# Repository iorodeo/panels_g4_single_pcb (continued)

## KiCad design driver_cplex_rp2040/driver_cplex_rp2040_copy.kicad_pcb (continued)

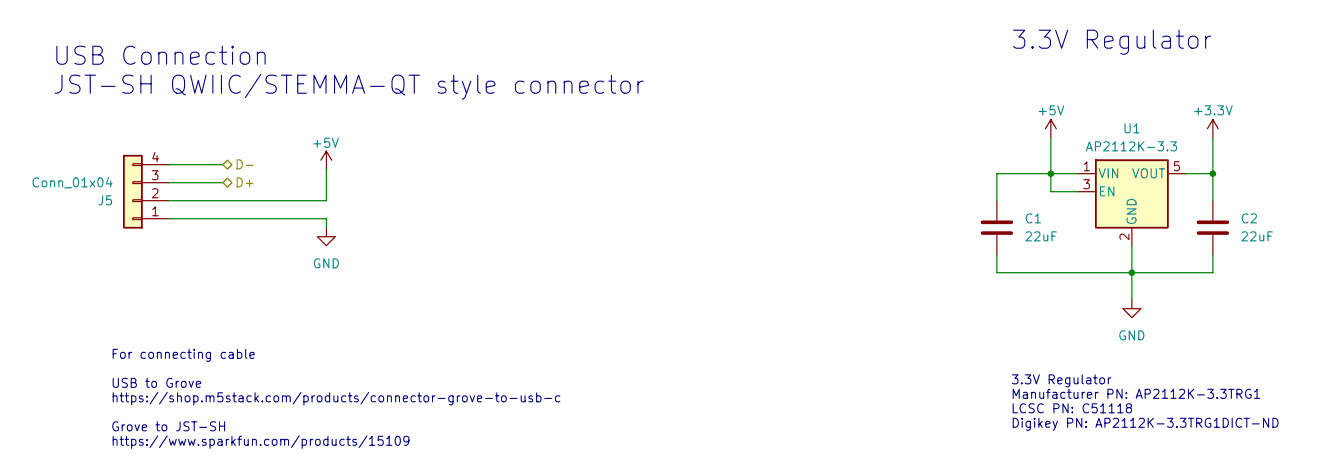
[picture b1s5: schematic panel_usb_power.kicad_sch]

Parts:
C1, C2: 22uF; C_0402_1005Metric
J5: Conn_01x04; JST_SH_SM04B-SRSS-TB_1x04-1MP_P1.00mm_Horizontal
U1: AP2112K-3.3; SOT-23-5

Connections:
+3.3V: C2.1, U1.5 (VOUT); also elsewhere on the board
+5V: C1.1, J5.2, U1.1 (VIN), U1.3 (EN); also elsewhere on the board
/panel_mcu/D+: J5.3; also elsewhere on the board
/panel_mcu/D-: J5.4; also elsewhere on the board
GND: C1.2, C2.2, J5.1, U1.2 (GND); also elsewhere on the board

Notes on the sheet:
USB Connection JST-SH QWIIC/STEMMA-QT style connector
For connecting cable USB to Grove https://shop.m5stack.com/products/connector-grove-to-usb-c Grove to JST-SH https://www.sparkfun.com/products/15109
3.3V Regulator
3.3V Regulator Manufacturer PN: AP2112K-3.3TRG1 LCSC PN: C51118 Digikey PN: AP2112K-3.3TRG1DICT-ND

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
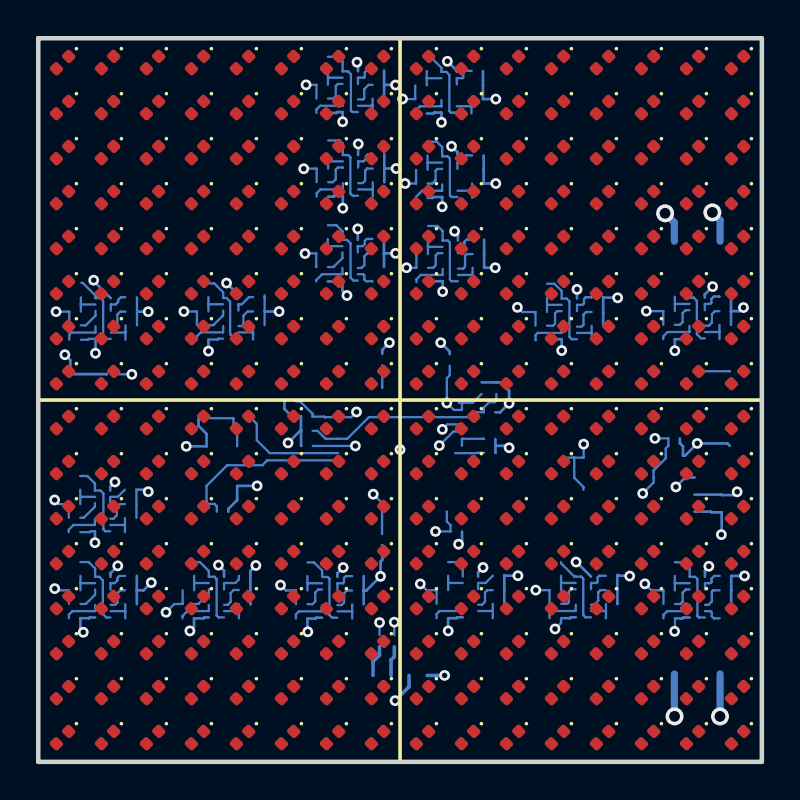
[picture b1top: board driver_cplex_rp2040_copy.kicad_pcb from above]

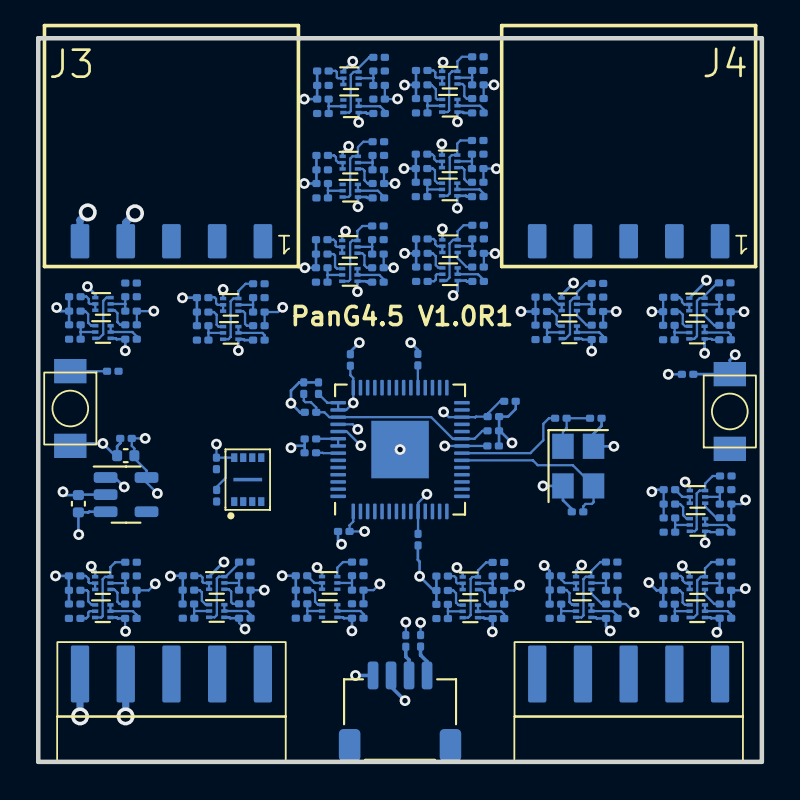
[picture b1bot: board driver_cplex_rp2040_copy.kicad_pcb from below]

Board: 6 copper layers, 40.2 x 40.2 mm, 479 parts (223 on the bottom side), 178 nets.

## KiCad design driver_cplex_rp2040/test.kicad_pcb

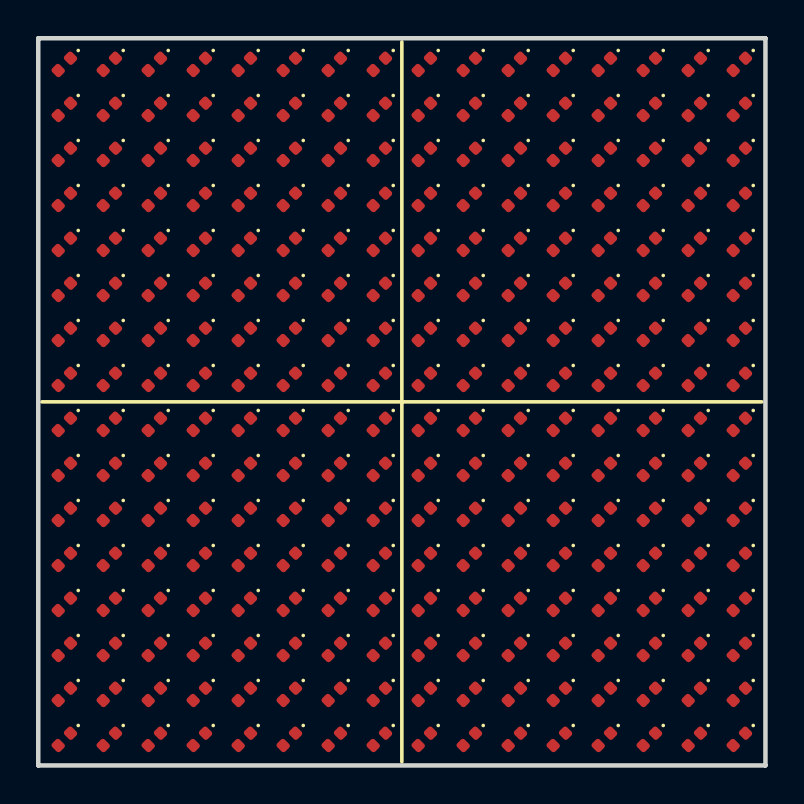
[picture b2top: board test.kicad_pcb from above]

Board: 6 copper layers, 40.4 x 40.4 mm, 256 parts (0 on the bottom side), 32 nets, no tracks yet.

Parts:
D1, D2, D3, D4, D5, D6, D7, D8, D9, D10, D11, D12, D13, D14, D15, D16, D17, D18, D19, D20, D21, D22, D23, D24, D25, D26, D27, D28, D29, D30, D31, D32, D33, D34, D35, D36, D37, D38, D39, D40, D41, D42, D43, D44, D45, D46, D47, D48, D49, D50, D51, D52, D53, D54, D55, D56, D57, D58, D59, D60, D61, D62, D63, D64, D65, D66, D67, D68, D69, D70, D71, D72, D73, D74, D75, D76, D77, D78, D79, D80, D81, D82, D83, D84, D85, D86, D87, D88, D89, D90, D91, D92, D93, D94, D95, D96, D97, D98, D99, D100, D101, D102, D103, D104, D105, D106, D107, D108, D109, D110, D111, D112, D113, D114, D115, D116, D117, D118, D119, D120, D121, D122, D123, D124, D125, D126, D127, D128, D129, D130, D131, D132, D133, D134, D135, D136, D137, D138, D139, D140, D141, D142, D143, D144, D145, D146, D147, D148, D149, D150, D151, D152, D153, D154, D155, D156, D157, D158, D159, D160, D161, D162, D163, D164, D165, D166, D167, D168, D169, D170, D171, D172, D173, D174, D175, D176, D177, D178, D179, D180, D181, D182, D183, D184, D185, D186, D187, D188, D189, D190, D191, D192, D193, D194, D195, D196, D197, D198, D199, D200, D201, D202, D203, D204, D205, D206, D207, D208, D209, D210, D211, D212, D213, D214, D215, D216, D217, D218, D219, D220, D221, D222, D223, D224, D225, D226, D227, D228, D229, D230, D231, D232, D233, D234, D235, D236, D237, D238, D239, D240, D241, D242, D243, D244, D245, D246, D247, D248, D249, D250, D251, D252, D253, D254, D255, D256: LED; LED_0402_1005Metric

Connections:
/panel_leds/ROW_00: D1.1 (K), D17.1 (K), D33.1 (K), D49.1 (K), D65.1 (K), D81.1 (K), D97.1 (K), D113.1 (K), D129.1 (K), D145.1 (K), D161.1 (K), D177.1 (K), D193.1 (K), D209.1 (K), D225.1 (K), D241.1 (K)
/panel_leds/ROW_01: D2.1 (K), D18.1 (K), D34.1 (K), D50.1 (K), D66.1 (K), D82.1 (K), D98.1 (K), D114.1 (K), D130.1 (K), D146.1 (K), D162.1 (K), D178.1 (K), D194.1 (K), D210.1 (K), D226.1 (K), D242.1 (K)
/panel_leds/ROW_02: D3.1 (K), D19.1 (K), D35.1 (K), D51.1 (K), D67.1 (K), D83.1 (K), D99.1 (K), D115.1 (K), D131.1 (K), D147.1 (K), D163.1 (K), D179.1 (K), D195.1 (K), D211.1 (K), D227.1 (K), D243.1 (K)
/panel_leds/ROW_03: D4.1 (K), D20.1 (K), D36.1 (K), D52.1 (K), D68.1 (K), D84.1 (K), D100.1 (K), D116.1 (K), D132.1 (K), D148.1 (K), D164.1 (K), D180.1 (K), D196.1 (K), D212.1 (K), D228.1 (K), D244.1 (K)
/panel_leds/ROW_04: D5.1 (K), D21.1 (K), D37.1 (K), D53.1 (K), D69.1 (K), D85.1 (K), D101.1 (K), D117.1 (K), D133.1 (K), D149.1 (K), D165.1 (K), D181.1 (K), D197.1 (K), D213.1 (K), D229.1 (K), D245.1 (K)
/panel_leds/ROW_05: D6.1 (K), D22.1 (K), D38.1 (K), D54.1 (K), D70.1 (K), D86.1 (K), D102.1 (K), D118.1 (K), D134.1 (K), D150.1 (K), D166.1 (K), D182.1 (K), D198.1 (K), D214.1 (K), D230.1 (K), D246.1 (K)
/panel_leds/ROW_06: D7.1 (K), D23.1 (K), D39.1 (K), D55.1 (K), D71.1 (K), D87.1 (K), D103.1 (K), D119.1 (K), D135.1 (K), D151.1 (K), D167.1 (K), D183.1 (K), D199.1 (K), D215.1 (K), D231.1 (K), D247.1 (K)
/panel_leds/ROW_07: D8.1 (K), D24.1 (K), D40.1 (K), D56.1 (K), D72.1 (K), D88.1 (K), D104.1 (K), D120.1 (K), D136.1 (K), D152.1 (K), D168.1 (K), D184.1 (K), D200.1 (K), D216.1 (K), D232.1 (K), D248.1 (K)
/panel_leds/ROW_08: D9.1 (K), D25.1 (K), D41.1 (K), D57.1 (K), D73.1 (K), D89.1 (K), D105.1 (K), D121.1 (K), D137.1 (K), D153.1 (K), D169.1 (K), D185.1 (K), D201.1 (K), D217.1 (K), D233.1 (K), D249.1 (K)
/panel_leds/ROW_09: D10.1 (K), D26.1 (K), D42.1 (K), D58.1 (K), D74.1 (K), D90.1 (K), D106.1 (K), D122.1 (K), D138.1 (K), D154.1 (K), D170.1 (K), D186.1 (K), D202.1 (K), D218.1 (K), D234.1 (K), D250.1 (K)
/panel_leds/ROW_10: D11.1 (K), D27.1 (K), D43.1 (K), D59.1 (K), D75.1 (K), D91.1 (K), D107.1 (K), D123.1 (K), D139.1 (K), D155.1 (K), D171.1 (K), D187.1 (K), D203.1 (K), D219.1 (K), D235.1 (K), D251.1 (K)
/panel_leds/ROW_11: D12.1 (K), D28.1 (K), D44.1 (K), D60.1 (K), D76.1 (K), D92.1 (K), D108.1 (K), D124.1 (K), D140.1 (K), D156.1 (K), D172.1 (K), D188.1 (K), D204.1 (K), D220.1 (K), D236.1 (K), D252.1 (K)
/panel_leds/ROW_12: D13.1 (K), D29.1 (K), D45.1 (K), D61.1 (K), D77.1 (K), D93.1 (K), D109.1 (K), D125.1 (K), D141.1 (K), D157.1 (K), D173.1 (K), D189.1 (K), D205.1 (K), D221.1 (K), D237.1 (K), D253.1 (K)
/panel_leds/ROW_13: D14.1 (K), D30.1 (K), D46.1 (K), D62.1 (K), D78.1 (K), D94.1 (K), D110.1 (K), D126.1 (K), D142.1 (K), D158.1 (K), D174.1 (K), D190.1 (K), D206.1 (K), D222.1 (K), D238.1 (K), D254.1 (K)
/panel_leds/ROW_14: D15.1 (K), D31.1 (K), D47.1 (K), D63.1 (K), D79.1 (K), D95.1 (K), D111.1 (K), D127.1 (K), D143.1 (K), D159.1 (K), D175.1 (K), D191.1 (K), D207.1 (K), D223.1 (K), D239.1 (K), D255.1 (K)
/panel_leds/ROW_15: D16.1 (K), D32.1 (K), D48.1 (K), D64.1 (K), D80.1 (K), D96.1 (K), D112.1 (K), D128.1 (K), D144.1 (K), D160.1 (K), D176.1 (K), D192.1 (K), D208.1 (K), D224.1 (K), D240.1 (K), D256.1 (K)
unnamed: D1.2 (A), D2.2 (A), D3.2 (A), D4.2 (A), D5.2 (A), D6.2 (A), D7.2 (A), D8.2 (A), D9.2 (A), D10.2 (A), D11.2 (A), D12.2 (A), D13.2 (A), D14.2 (A), D15.2 (A), D16.2 (A)
unnamed: D17.2 (A), D18.2 (A), D19.2 (A), D20.2 (A), D21.2 (A), D22.2 (A), D23.2 (A), D24.2 (A), D25.2 (A), D26.2 (A), D27.2 (A), D28.2 (A), D29.2 (A), D30.2 (A), D31.2 (A), D32.2 (A)
unnamed: D33.2 (A), D34.2 (A), D35.2 (A), D36.2 (A), D37.2 (A), D38.2 (A), D39.2 (A), D40.2 (A), D41.2 (A), D42.2 (A), D43.2 (A), D44.2 (A), D45.2 (A), D46.2 (A), D47.2 (A), D48.2 (A)
unnamed: D49.2 (A), D50.2 (A), D51.2 (A), D52.2 (A), D53.2 (A), D54.2 (A), D55.2 (A), D56.2 (A), D57.2 (A), D58.2 (A), D59.2 (A), D60.2 (A), D61.2 (A), D62.2 (A), D63.2 (A), D64.2 (A)
unnamed: D65.2 (A), D66.2 (A), D67.2 (A), D68.2 (A), D69.2 (A), D70.2 (A), D71.2 (A), D72.2 (A), D73.2 (A), D74.2 (A), D75.2 (A), D76.2 (A), D77.2 (A), D78.2 (A), D79.2 (A), D80.2 (A)
unnamed: D81.2 (A), D82.2 (A), D83.2 (A), D84.2 (A), D85.2 (A), D86.2 (A), D87.2 (A), D88.2 (A), D89.2 (A), D90.2 (A), D91.2 (A), D92.2 (A), D93.2 (A), D94.2 (A), D95.2 (A), D96.2 (A)
unnamed: D97.2 (A), D98.2 (A), D99.2 (A), D100.2 (A), D101.2 (A), D102.2 (A), D103.2 (A), D104.2 (A), D105.2 (A), D106.2 (A), D107.2 (A), D108.2 (A), D109.2 (A), D110.2 (A), D111.2 (A), D112.2 (A)
unnamed: D113.2 (A), D114.2 (A), D115.2 (A), D116.2 (A), D117.2 (A), D118.2 (A), D119.2 (A), D120.2 (A), D121.2 (A), D122.2 (A), D123.2 (A), D124.2 (A), D125.2 (A), D126.2 (A), D127.2 (A), D128.2 (A)
unnamed: D129.2 (A), D130.2 (A), D131.2 (A), D132.2 (A), D133.2 (A), D134.2 (A), D135.2 (A), D136.2 (A), D137.2 (A), D138.2 (A), D139.2 (A), D140.2 (A), D141.2 (A), D142.2 (A), D143.2 (A), D144.2 (A)
unnamed: D145.2 (A), D146.2 (A), D147.2 (A), D148.2 (A), D149.2 (A), D150.2 (A), D151.2 (A), D152.2 (A), D153.2 (A), D154.2 (A), D155.2 (A), D156.2 (A), D157.2 (A), D158.2 (A), D159.2 (A), D160.2 (A)
unnamed: D161.2 (A), D162.2 (A), D163.2 (A), D164.2 (A), D165.2 (A), D166.2 (A), D167.2 (A), D168.2 (A), D169.2 (A), D170.2 (A), D171.2 (A), D172.2 (A), D173.2 (A), D174.2 (A), D175.2 (A), D176.2 (A)
unnamed: D177.2 (A), D178.2 (A), D179.2 (A), D180.2 (A), D181.2 (A), D182.2 (A), D183.2 (A), D184.2 (A), D185.2 (A), D186.2 (A), D187.2 (A), D188.2 (A), D189.2 (A), D190.2 (A), D191.2 (A), D192.2 (A)
unnamed: D193.2 (A), D194.2 (A), D195.2 (A), D196.2 (A), D197.2 (A), D198.2 (A), D199.2 (A), D200.2 (A), D201.2 (A), D202.2 (A), D203.2 (A), D204.2 (A), D205.2 (A), D206.2 (A), D207.2 (A), D208.2 (A)
unnamed: D209.2 (A), D210.2 (A), D211.2 (A), D212.2 (A), D213.2 (A), D214.2 (A), D215.2 (A), D216.2 (A), D217.2 (A), D218.2 (A), D219.2 (A), D220.2 (A), D221.2 (A), D222.2 (A), D223.2 (A), D224.2 (A)
unnamed: D225.2 (A), D226.2 (A), D227.2 (A), D228.2 (A), D229.2 (A), D230.2 (A), D231.2 (A), D232.2 (A), D233.2 (A), D234.2 (A), D235.2 (A), D236.2 (A), D237.2 (A), D238.2 (A), D239.2 (A), D240.2 (A)
unnamed: D241.2 (A), D242.2 (A), D243.2 (A), D244.2 (A), D245.2 (A), D246.2 (A), D247.2 (A), D248.2 (A), D249.2 (A), D250.2 (A), D251.2 (A), D252.2 (A), D253.2 (A), D254.2 (A), D255.2 (A), D256.2 (A)

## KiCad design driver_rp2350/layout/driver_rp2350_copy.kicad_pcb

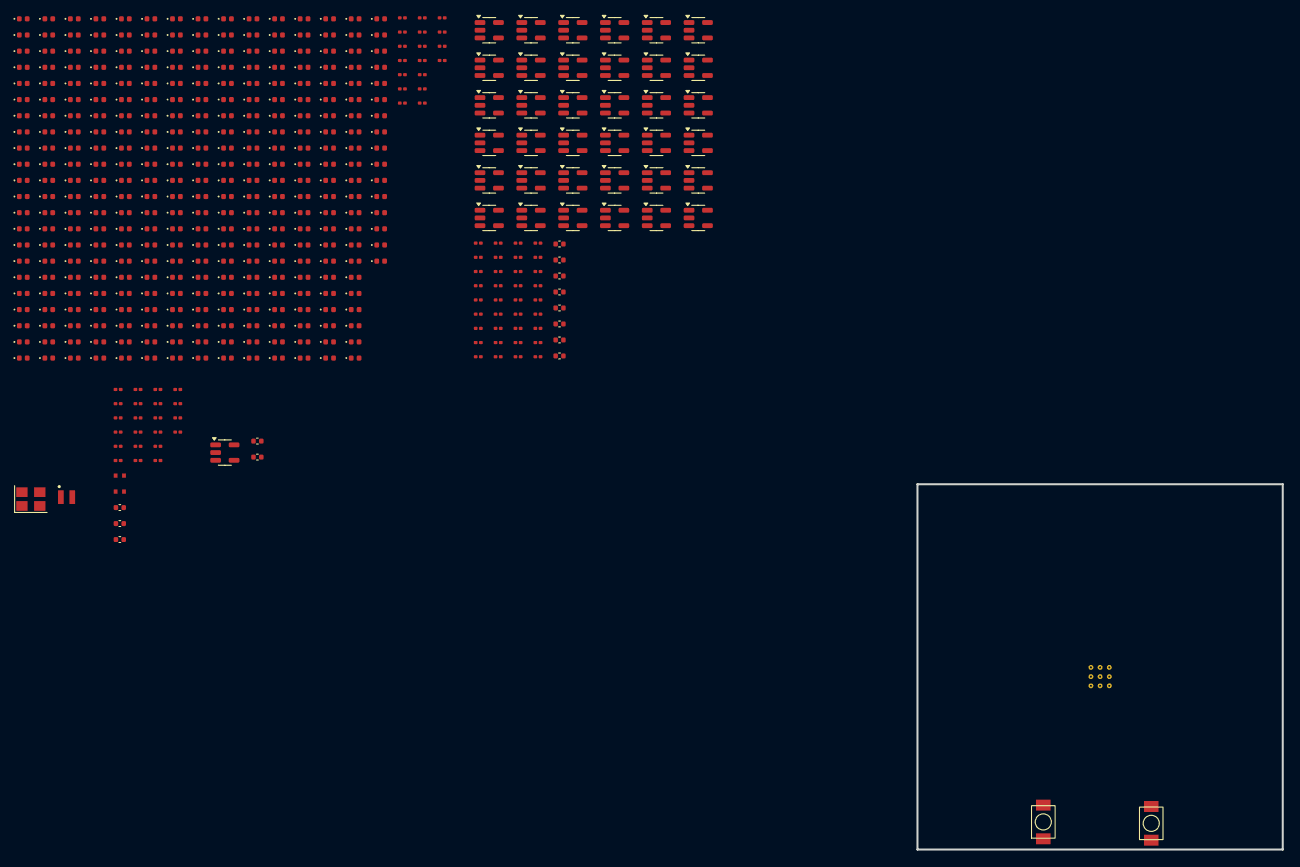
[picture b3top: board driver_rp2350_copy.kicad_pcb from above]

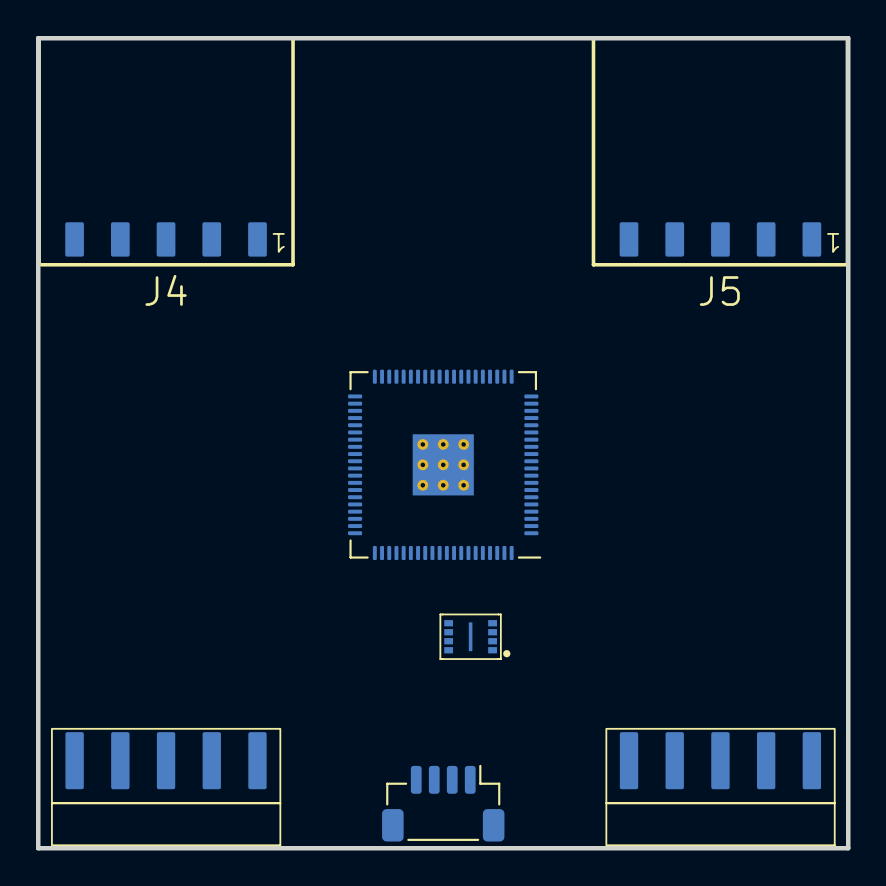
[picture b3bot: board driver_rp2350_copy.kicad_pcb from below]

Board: 6 copper layers, 45.0 x 45.0 mm, 463 parts (7 on the bottom side), 121 nets, no tracks yet.

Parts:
C1, C2: 15pF; C_0201_0603Metric
C3, C6, C9, C10, C11, C12, C13, C14, C15, C16, C17, C18, C20, C21, C22, C23, C24, C25, C26, C27, C28, C29, C30, C31, C32, C33, C34, C35, C36, C37, C38, C39, C40, C41, C42, C43, C44, C45, C46, C47, C48, C49, C50, C51, C52, C53, C54, C55: 100nF; C_0201_0603Metric
C4, C5: 4.7uF; C_0402_1005Metric_small_pads
C7, C8: 4.7uF; C_0402_1005Metric
C19, C56, C57, C58, C59, C60, C61, C62, C63, C64, C65: 10uF; C_0402_1005Metric
D_0A1, D_0B1, D_0C1, D_0D1, D_0E1, D_0F1, D_0G1, D_0H1, D_1, D_1A1, D_1B1, D_1C1, D_1D1, D_1E1, D_1F1, D_1G1, D_1H1, D_2, D_2A1, D_2B1, D_2C1, D_2D1, D_2E1, D_2F1, D_2G1, D_2H1, D_3, D_3A1, D_3B1, D_3C1, D_3D1, D_3E1, D_3F1, D_3G1, D_3H1, D_4, D_4A1, D_4B1, D_4C1, D_4D1, D_4E1, D_4F1, D_4G1, D_4H1, D_5, D_5A1, D_5B1, D_5C1, D_5D1, D_5E1, D_5F1, D_5G1, D_5H1, D_6, D_6A1, D_6B1, D_6C1, D_6D1, D_6E1, D_6F1, D_6G1, D_6H1, D_7, D_7A1, D_7B1, D_7C1, D_7D1, D_7E1, D_7F1, D_7G1, D_7H1, D_8, D_8A1, D_8B1, D_8C1, D_8D1, D_8E1, D_8F1, D_8G1, D_8H1, D_9, D_9A1, D_9B1, D_9C1, D_9D1, D_9E1, D_9F1, D_9G1, D_9H1, D_10, D_11, D_12, D_13, D_14, D_15, D_16, D_17, D_18, D_19, D_20, D_21, D_22, D_23, D_24, D_25, D_26, D_27, D_28, D_29, D_30, D_31, D_32, D_33, D_34, D_35, D_36, D_37, D_38, D_39, D_40, D_41, D_42, D_43, D_44, D_45, D_46, D_47, D_48, D_49, D_50, D_51, D_52, D_53, D_54, D_55, D_56, D_57, D_58, D_59, D_60, D_61, D_62, D_63, D_64, D_65, D_66, D_67, D_68, D_69, D_70, D_71, D_72, D_73, D_74, D_75, D_76, D_77, D_78, D_79, D_80, D_81, D_82, D_83, D_84, D_85, D_86, D_87, D_88, D_89, D_90, D_91, D_92, D_93, D_94, D_95, D_96, D_97, D_98, D_99, D_100: LED; LED_0402_1005Metric
D_A1, D_A2, D_A3, D_A4, D_A5, D_A6, D_A7, D_A8, D_A9, D_A10: LED; LED_0402_1005Metric
D_AA1: LED; LED_0402_1005Metric
D_AB1: LED; LED_0402_1005Metric
D_AC1: LED; LED_0402_1005Metric
D_AD1: LED; LED_0402_1005Metric
D_AE1: LED; LED_0402_1005Metric
D_AF1: LED; LED_0402_1005Metric
D_AG1: LED; LED_0402_1005Metric
D_AH1: LED; LED_0402_1005Metric
D_B1, D_B2, D_B3, D_B4, D_B5, D_B6, D_B7, D_B8, D_B9, D_B10: LED; LED_0402_1005Metric
D_BA1: LED; LED_0402_1005Metric
D_BB1: LED; LED_0402_1005Metric
D_BC1: LED; LED_0402_1005Metric
D_BD1: LED; LED_0402_1005Metric
D_BE1: LED; LED_0402_1005Metric
D_BF1: LED; LED_0402_1005Metric
D_BG1: LED; LED_0402_1005Metric
D_BH1: LED; LED_0402_1005Metric
D_C1, D_C2, D_C3, D_C4, D_C5, D_C6, D_C7, D_C8, D_C9, D_C10: LED; LED_0402_1005Metric
D_CA1: LED; LED_0402_1005Metric
D_CB1: LED; LED_0402_1005Metric
D_CC1: LED; LED_0402_1005Metric
D_CD1: LED; LED_0402_1005Metric
D_CE1: LED; LED_0402_1005Metric
D_CF1: LED; LED_0402_1005Metric
D_CG1: LED; LED_0402_1005Metric
D_CH1: LED; LED_0402_1005Metric
D_D1, D_D2, D_D3, D_D4, D_D5, D_D6, D_D7, D_D8, D_D9, D_D10: LED; LED_0402_1005Metric
D_DA1: LED; LED_0402_1005Metric
D_DB1: LED; LED_0402_1005Metric
D_DC1: LED; LED_0402_1005Metric
D_DD1: LED; LED_0402_1005Metric
D_DE1: LED; LED_0402_1005Metric
D_DF1: LED; LED_0402_1005Metric
D_DG1: LED; LED_0402_1005Metric
D_DH1: LED; LED_0402_1005Metric
D_E1, D_E2, D_E3, D_E4, D_E5, D_E6, D_E7, D_E8, D_E9, D_E10: LED; LED_0402_1005Metric
D_EA1: LED; LED_0402_1005Metric
D_EB1: LED; LED_0402_1005Metric
D_EC1: LED; LED_0402_1005Metric
D_ED1: LED; LED_0402_1005Metric
D_EE1: LED; LED_0402_1005Metric
D_EF1: LED; LED_0402_1005Metric
D_EG1: LED; LED_0402_1005Metric
D_EH1: LED; LED_0402_1005Metric
D_F1, D_F2, D_F3, D_F4, D_F5, D_F6, D_F7, D_F8, D_F9, D_F10: LED; LED_0402_1005Metric
D_FA1: LED; LED_0402_1005Metric
D_FB1: LED; LED_0402_1005Metric
D_FC1: LED; LED_0402_1005Metric
D_FD1: LED; LED_0402_1005Metric
D_FE1: LED; LED_0402_1005Metric
D_FF1: LED; LED_0402_1005Metric
D_FG1: LED; LED_0402_1005Metric
D_FH1: LED; LED_0402_1005Metric
D_G1, D_G2, D_G3, D_G4, D_G5, D_G6, D_G7, D_G8, D_G9, D_G10: LED; LED_0402_1005Metric
D_GA1: LED; LED_0402_1005Metric
D_GB1: LED; LED_0402_1005Metric
D_GC1: LED; LED_0402_1005Metric
D_GD1: LED; LED_0402_1005Metric
D_GE1: LED; LED_0402_1005Metric
D_GF1: LED; LED_0402_1005Metric
D_GG1: LED; LED_0402_1005Metric
D_GH1: LED; LED_0402_1005Metric
D_H1, D_H2, D_H3, D_H4, D_H5, D_H6, D_H7, D_H8, D_H9, D_H10: LED; LED_0402_1005Metric
D_HA1: LED; LED_0402_1005Metric
D_HB1: LED; LED_0402_1005Metric
D_HC1: LED; LED_0402_1005Metric
D_HD1: LED; LED_0402_1005Metric
D_HE1: LED; LED_0402_1005Metric
D_HF1: LED; LED_0402_1005Metric
D_HG1: LED; LED_0402_1005Metric
D_HH1: LED; LED_0402_1005Metric
J1: Conn_01x04; JST_SH_BM04B-SRSS-TB_1x04-1MP_P1.00mm_Vertical
J2, J3: Conn_01x05; PinHeader_1x5_M20-8890545R
J4, J5: Conn_01x05; ConnRcpt_1x5_SMH-105-02-X-S
L1: 3.3uH; L_pol_2016
R1, R4: 10k; R_0201_0603Metric
R2, R3, R5: 1k; R_0201_0603Metric
R6: 33; R_0201_0603Metric
R7, R8: 27; R_0201_0603Metric
R9, R10, R11, R12, R13, R14, R15, R16, R17, R18, R19, R20, R21, R22, R23, R24, R25, R26: 270; R_0201_0603Metric
SW1, SW2: SW_Push; TS-1088-AR02016
U1: APS6404L-3SQR; flashmem_PSON50P300X200X60-9N
U2: RP2354B_80QFN; RP2350-QFN-80-1EP_10x10_P0.4mm_EP3.4x3.4mm_ThermalVias
U3, U4, U5, U6, U7, U8, U9, U10, U11, U12, U13, U14, U15, U16, U17, U18, U19, U20, U21, U22, U23, U24, U25, U26, U27, U28, U29, U30, U31, U32, U33, U34, U35, U36, U37, U38: UCC27517; SOT-23-5
U39: AP2112K-3.3; SOT-23-5
Y1: ABM8-272-T3; Crystal_SMD_3225-4Pin_3.2x2.5mm

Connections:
+1V1: C5.1, C6.1, C8.1, C9.1, L1.1, U2.10 (DVDD), U2.32 (DVDD), U2.51 (DVDD), U2.65 (VREG_FB)
+3V3: C3.1, C4.1, C10.1, C11.1, C12.1, C13.1, C14.1, C15.1, C16.1, C17.1, C18.1, C19.1, C65.1, R1.1, R4.1, R6.1, U1.8 (VCC), U2.5 (IOVDD), U2.15 (IOVDD), U2.24 (IOVDD), U2.29 (IOVDD), U2.41 (IOVDD), U2.50 (IOVDD), U2.59 (ADC_AVDD), U2.60 (IOVDD), U2.64 (VREG_VIN), U2.68 (USB_OTP_VDD), U2.69 (QSPI_IOVDD), U2.76 (IOVDD), U39.5 (VOUT)
+5V: C20.1, C21.1, C22.1, C23.1, C24.1, C25.1, C26.1, C27.1, C28.1, C29.1, C30.1, C31.1, C32.1, C33.1, C34.1, C35.1, C36.1, C37.1, C38.1, C39.1, C40.1, C41.1, C42.1, C43.1, C44.1, C45.1, C46.1, C47.1, C48.1, C49.1, C50.1, C51.1, C52.1, C53.1, C54.1, C55.1, C56.1, C57.1, C58.1, C59.1, C60.1, C61.1, C62.1, C63.1, C64.1, J1.2, J2.5, J4.5, U3.1 (VDD), U4.1 (VDD), U5.1 (VDD), U6.1 (VDD), U7.1 (VDD), U8.1 (VDD), U9.1 (VDD), U10.1 (VDD), U11.1 (VDD), U12.1 (VDD), U13.1 (VDD), U14.1 (VDD), U15.1 (VDD), U16.1 (VDD), U17.1 (VDD), U18.1 (VDD), U19.1 (VDD), U20.1 (VDD), U21.1 (VDD), U22.1 (VDD), U23.1 (VDD), U24.1 (VDD), U25.1 (VDD), U26.1 (VDD), U27.1 (VDD), U28.1 (VDD), U29.1 (VDD), U30.1 (VDD), U31.1 (VDD), U32.1 (VDD), U33.1 (VDD), U34.1 (VDD), U35.1 (VDD), U36.1 (VDD), U37.1 (VDD), U38.1 (VDD), U39.1 (VIN), U39.3 (EN)
/drivers/COL_0: R9.1, U3.5 (OUT)
/drivers/COL_1: R10.1, U4.5 (OUT)
/drivers/COL_2: R11.1, U5.5 (OUT)
/drivers/COL_3: R12.1, U6.5 (OUT)
/drivers/COL_4: R13.1, U7.5 (OUT)
/drivers/COL_5: R14.1, U8.5 (OUT)
/drivers/COL_6: R15.1, U9.5 (OUT)
/drivers/COL_7: R16.1, U10.5 (OUT)
/drivers/COL_8: R17.1, U11.5 (OUT)
/drivers/COL_9: R18.1, U12.5 (OUT)
/drivers/COL_A: R19.1, U13.5 (OUT)
/drivers/COL_B: R20.1, U14.5 (OUT)
/drivers/COL_C: R21.1, U15.5 (OUT)
/drivers/COL_D: R22.1, U16.5 (OUT)
/drivers/COL_E: R23.1, U17.5 (OUT)
/drivers/COL_F: R24.1, U18.5 (OUT)
/drivers/COL_G: R25.1, U19.5 (OUT)
/drivers/COL_H: R26.1, U20.5 (OUT)
/drivers/COL_MCU_0: U2.78 (GPIO1), U3.3 (IN+)
/drivers/COL_MCU_1: U2.79 (GPIO2), U4.3 (IN+)
/drivers/COL_MCU_2: U2.80 (GPIO3), U5.3 (IN+)
/drivers/COL_MCU_3: U2.1 (GPIO4), U6.3 (IN+)
/drivers/COL_MCU_4: U2.2 (GPIO5), U7.3 (IN+)
/drivers/COL_MCU_5: U2.3 (GPIO6), U8.3 (IN+)
/drivers/COL_MCU_6: U2.4 (GPIO7), U9.3 (IN+)
/drivers/COL_MCU_7: U2.6 (GPIO8), U10.3 (IN+)
/drivers/COL_MCU_8: U2.7 (GPIO9), U11.3 (IN+)
/drivers/COL_MCU_9: U2.8 (GPIO10), U12.3 (IN+)
/drivers/COL_MCU_A: U2.9 (GPIO11), U13.3 (IN+)
/drivers/COL_MCU_B: U2.11 (GPIO12), U14.3 (IN+)
/drivers/COL_MCU_C: U2.12 (GPIO13), U15.3 (IN+)
/drivers/COL_MCU_D: U2.13 (GPIO14), U16.3 (IN+)
/drivers/COL_MCU_E: U2.14 (GPIO15), U17.3 (IN+)
/drivers/COL_MCU_F: U2.16 (GPIO16), U18.3 (IN+)
/drivers/COL_MCU_G: U2.17 (GPIO17), U19.3 (IN+)
/drivers/COL_MCU_H: U2.18 (GPIO18), U20.3 (IN+)
/drivers/ROW_0: D_0A1.1 (K), D_0B1.1 (K), D_0C1.1 (K), D_0D1.1 (K), D_0E1.1 (K), D_0F1.1 (K), D_0G1.1 (K), D_0H1.1 (K), D_1.1 (K), D_11.1 (K), D_21.1 (K), D_31.1 (K), D_41.1 (K), D_51.1 (K), D_61.1 (K), D_71.1 (K), D_81.1 (K), D_91.1 (K), U21.5 (OUT)
/drivers/ROW_1: D_1A1.1 (K), D_1B1.1 (K), D_1C1.1 (K), D_1D1.1 (K), D_1E1.1 (K), D_1F1.1 (K), D_1G1.1 (K), D_1H1.1 (K), D_2.1 (K), D_12.1 (K), D_22.1 (K), D_32.1 (K), D_42.1 (K), D_52.1 (K), D_62.1 (K), D_72.1 (K), D_82.1 (K), D_92.1 (K), U22.5 (OUT)
/drivers/ROW_2: D_2A1.1 (K), D_2B1.1 (K), D_2C1.1 (K), D_2D1.1 (K), D_2E1.1 (K), D_2F1.1 (K), D_2G1.1 (K), D_2H1.1 (K), D_3.1 (K), D_13.1 (K), D_23.1 (K), D_33.1 (K), D_43.1 (K), D_53.1 (K), D_63.1 (K), D_73.1 (K), D_83.1 (K), D_93.1 (K), U23.5 (OUT)
/drivers/ROW_3: D_3A1.1 (K), D_3B1.1 (K), D_3C1.1 (K), D_3D1.1 (K), D_3E1.1 (K), D_3F1.1 (K), D_3G1.1 (K), D_3H1.1 (K), D_4.1 (K), D_14.1 (K), D_24.1 (K), D_34.1 (K), D_44.1 (K), D_54.1 (K), D_64.1 (K), D_74.1 (K), D_84.1 (K), D_94.1 (K), U24.5 (OUT)
/drivers/ROW_4: D_4A1.1 (K), D_4B1.1 (K), D_4C1.1 (K), D_4D1.1 (K), D_4E1.1 (K), D_4F1.1 (K), D_4G1.1 (K), D_4H1.1 (K), D_5.1 (K), D_15.1 (K), D_25.1 (K), D_35.1 (K), D_45.1 (K), D_55.1 (K), D_65.1 (K), D_75.1 (K), D_85.1 (K), D_95.1 (K), U25.5 (OUT)
/drivers/ROW_5: D_5A1.1 (K), D_5B1.1 (K), D_5C1.1 (K), D_5D1.1 (K), D_5E1.1 (K), D_5F1.1 (K), D_5G1.1 (K), D_5H1.1 (K), D_6.1 (K), D_16.1 (K), D_26.1 (K), D_36.1 (K), D_46.1 (K), D_56.1 (K), D_66.1 (K), D_76.1 (K), D_86.1 (K), D_96.1 (K), U26.5 (OUT)
/drivers/ROW_6: D_6A1.1 (K), D_6B1.1 (K), D_6C1.1 (K), D_6D1.1 (K), D_6E1.1 (K), D_6F1.1 (K), D_6G1.1 (K), D_6H1.1 (K), D_7.1 (K), D_17.1 (K), D_27.1 (K), D_37.1 (K), D_47.1 (K), D_57.1 (K), D_67.1 (K), D_77.1 (K), D_87.1 (K), D_97.1 (K), U27.5 (OUT)
/drivers/ROW_7: D_7A1.1 (K), D_7B1.1 (K), D_7C1.1 (K), D_7D1.1 (K), D_7E1.1 (K), D_7F1.1 (K), D_7G1.1 (K), D_7H1.1 (K), D_8.1 (K), D_18.1 (K), D_28.1 (K), D_38.1 (K), D_48.1 (K), D_58.1 (K), D_68.1 (K), D_78.1 (K), D_88.1 (K), D_98.1 (K), U28.5 (OUT)
/drivers/ROW_8: D_8A1.1 (K), D_8B1.1 (K), D_8C1.1 (K), D_8D1.1 (K), D_8E1.1 (K), D_8F1.1 (K), D_8G1.1 (K), D_8H1.1 (K), D_9.1 (K), D_19.1 (K), D_29.1 (K), D_39.1 (K), D_49.1 (K), D_59.1 (K), D_69.1 (K), D_79.1 (K), D_89.1 (K), D_99.1 (K), U29.5 (OUT)
/drivers/ROW_9: D_9A1.1 (K), D_9B1.1 (K), D_9C1.1 (K), D_9D1.1 (K), D_9E1.1 (K), D_9F1.1 (K), D_9G1.1 (K), D_9H1.1 (K), D_10.1 (K), D_20.1 (K), D_30.1 (K), D_40.1 (K), D_50.1 (K), D_60.1 (K), D_70.1 (K), D_80.1 (K), D_90.1 (K), D_100.1 (K), U30.5 (OUT)
/drivers/ROW_A: D_A1.1 (K), D_A2.1 (K), D_A3.1 (K), D_A4.1 (K), D_A5.1 (K), D_A6.1 (K), D_A7.1 (K), D_A8.1 (K), D_A9.1 (K), D_A10.1 (K), D_AA1.1 (K), D_AB1.1 (K), D_AC1.1 (K), D_AD1.1 (K), D_AE1.1 (K), D_AF1.1 (K), D_AG1.1 (K), D_AH1.1 (K), U31.5 (OUT)
/drivers/ROW_B: D_B1.1 (K), D_B2.1 (K), D_B3.1 (K), D_B4.1 (K), D_B5.1 (K), D_B6.1 (K), D_B7.1 (K), D_B8.1 (K), D_B9.1 (K), D_B10.1 (K), D_BA1.1 (K), D_BB1.1 (K), D_BC1.1 (K), D_BD1.1 (K), D_BE1.1 (K), D_BF1.1 (K), D_BG1.1 (K), D_BH1.1 (K), U32.5 (OUT)
/drivers/ROW_C: D_C1.1 (K), D_C2.1 (K), D_C3.1 (K), D_C4.1 (K), D_C5.1 (K), D_C6.1 (K), D_C7.1 (K), D_C8.1 (K), D_C9.1 (K), D_C10.1 (K), D_CA1.1 (K), D_CB1.1 (K), D_CC1.1 (K), D_CD1.1 (K), D_CE1.1 (K), D_CF1.1 (K), D_CG1.1 (K), D_CH1.1 (K), U33.5 (OUT)
/drivers/ROW_D: D_D1.1 (K), D_D2.1 (K), D_D3.1 (K), D_D4.1 (K), D_D5.1 (K), D_D6.1 (K), D_D7.1 (K), D_D8.1 (K), D_D9.1 (K), D_D10.1 (K), D_DA1.1 (K), D_DB1.1 (K), D_DC1.1 (K), D_DD1.1 (K), D_DE1.1 (K), D_DF1.1 (K), D_DG1.1 (K), D_DH1.1 (K), U34.5 (OUT)
/drivers/ROW_E: D_E1.1 (K), D_E2.1 (K), D_E3.1 (K), D_E4.1 (K), D_E5.1 (K), D_E6.1 (K), D_E7.1 (K), D_E8.1 (K), D_E9.1 (K), D_E10.1 (K), D_EA1.1 (K), D_EB1.1 (K), D_EC1.1 (K), D_ED1.1 (K), D_EE1.1 (K), D_EF1.1 (K), D_EG1.1 (K), D_EH1.1 (K), U35.5 (OUT)
/drivers/ROW_F: D_F1.1 (K), D_F2.1 (K), D_F3.1 (K), D_F4.1 (K), D_F5.1 (K), D_F6.1 (K), D_F7.1 (K), D_F8.1 (K), D_F9.1 (K), D_F10.1 (K), D_FA1.1 (K), D_FB1.1 (K), D_FC1.1 (K), D_FD1.1 (K), D_FE1.1 (K), D_FF1.1 (K), D_FG1.1 (K), D_FH1.1 (K), U36.5 (OUT)
/drivers/ROW_G: D_G1.1 (K), D_G2.1 (K), D_G3.1 (K), D_G4.1 (K), D_G5.1 (K), D_G6.1 (K), D_G7.1 (K), D_G8.1 (K), D_G9.1 (K), D_G10.1 (K), D_GA1.1 (K), D_GB1.1 (K), D_GC1.1 (K), D_GD1.1 (K), D_GE1.1 (K), D_GF1.1 (K), D_GG1.1 (K), D_GH1.1 (K), U37.5 (OUT)
/drivers/ROW_H: D_H1.1 (K), D_H2.1 (K), D_H3.1 (K), D_H4.1 (K), D_H5.1 (K), D_H6.1 (K), D_H7.1 (K), D_H8.1 (K), D_H9.1 (K), D_H10.1 (K), D_HA1.1 (K), D_HB1.1 (K), D_HC1.1 (K), D_HD1.1 (K), D_HE1.1 (K), D_HF1.1 (K), D_HG1.1 (K), D_HH1.1 (K), U38.5 (OUT)
/drivers/ROW_MCU_0: U2.19 (GPIO19), U21.3 (IN+)
/drivers/ROW_MCU_1: U2.20 (GPIO20), U22.3 (IN+)
/drivers/ROW_MCU_2: U2.21 (GPIO21), U23.3 (IN+)
/drivers/ROW_MCU_3: U2.22 (GPIO22), U24.3 (IN+)
/drivers/ROW_MCU_4: U2.23 (GPIO23), U25.3 (IN+)
/drivers/ROW_MCU_5: U2.25 (GPIO24), U26.3 (IN+)
/drivers/ROW_MCU_6: U2.26 (GPIO25), U27.3 (IN+)
/drivers/ROW_MCU_7: U2.27 (GPIO26), U28.3 (IN+)
/drivers/ROW_MCU_8: U2.28 (GPIO27), U29.3 (IN+)
/drivers/ROW_MCU_9: U2.36 (GPIO28), U30.3 (IN+)
/drivers/ROW_MCU_A: U2.37 (GPIO29), U31.3 (IN+)
/drivers/ROW_MCU_B: U2.38 (GPIO30), U32.3 (IN+)
/drivers/ROW_MCU_C: U2.39 (GPIO31), U33.3 (IN+)
/drivers/ROW_MCU_D: U2.45 (GPIO36), U34.3 (IN+)
/drivers/ROW_MCU_E: U2.46 (GPIO37), U35.3 (IN+)
/drivers/ROW_MCU_F: U2.47 (GPIO38), U36.3 (IN+)
/drivers/ROW_MCU_G: U2.49 (GPIO40_ADC0), U37.3 (IN+)
/drivers/ROW_MCU_H: U2.48 (GPIO39), U38.3 (IN+)
/panel_header/CS0: J3.5, U2.42 (GPIO33)
/panel_header/CS1: J3.4, J5.5
/panel_header/CS2: J3.3, J5.4
/panel_header/CS4: J3.2, J5.3
/panel_header/EINT: J3.1, J5.1
/panel_header/MISO: J2.1, J4.1, U2.44 (GPIO35)
/panel_header/MOSI: J2.2, J4.2, U2.40 (GPIO32)
/panel_header/SCK: J2.3, J4.3, U2.43 (GPIO34)
/panel_mcu/D+: J1.3, R7.1
/panel_mcu/D-: J1.4, R8.1
/panel_mcu/QSPI_SCLK: U1.6 (CLK), U2.71 (QSPI_SCLK)
/panel_mcu/QSPI_SD0: U1.5 (IO0), U2.72 (QSPI_SD0)
/panel_mcu/QSPI_SD1: U1.2 (IO1), U2.74 (QSPI_SD1)
/panel_mcu/QSPI_SD2: U1.3 (IO2), U2.73 (QSPI_SD2)
/panel_mcu/QSPI_SD3: U1.7 (IO3), U2.70 (QSPI_SD3)
/panel_mcu/QSPI_SS: R3.1, R4.2, U2.75 (QSPI_SS)
/panel_mcu/RUN: SW2.2, U2.35 (RUN)
/panel_mcu/VREG_AVDD: C7.1, R6.2, U2.61 (VREG_AVDD)
/panel_mcu/VREG_LX: L1.2, U2.63 (VREG_LX)
/panel_mcu/XIN: C1.1, U2.30 (XIN), Y1.1
/panel_mcu/XIP_CS1n: R1.2, U1.1 (~CS), U2.77 (GPIO0)
/panel_mcu/XOUT: R5.1, U2.31 (XOUT)
/panel_mcu/~USB_BOOT: R3.2, SW1.2
GND: C1.2, C2.2, C3.2, C4.2, C5.2, C6.2, C7.2, C8.2, C9.2, C10.2, C11.2, C12.2, C13.2, C14.2, C15.2, C16.2, C17.2, C18.2, C19.2, C20.2, C21.2, C22.2, C23.2, C24.2, C25.2, C26.2, C27.2, C28.2, C29.2, C30.2, C31.2, C32.2, C33.2, C34.2, C35.2, C36.2, C37.2, C38.2, C39.2, C40.2, C41.2, C42.2, C43.2, C44.2, C45.2, C46.2, C47.2, C48.2, C49.2, C50.2, C51.2, C52.2, C53.2, C54.2, C55.2, C56.2, C57.2, C58.2, C59.2, C60.2, C61.2, C62.2, C63.2, C64.2, C65.2, J1.1, J2.4, J4.4, R2.2, SW1.1, U1.4 (GND), U2.62 (VREG_PGND), U2.81 (GND), U3.2 (GND), U3.4 (IN-), U4.2 (GND), U4.4 (IN-), U5.2 (GND), U5.4 (IN-), U6.2 (GND), U6.4 (IN-), U7.2 (GND), U7.4 (IN-), U8.2 (GND), U8.4 (IN-), U9.2 (GND), U9.4 (IN-), U10.2 (GND), U10.4 (IN-), U11.2 (GND), U11.4 (IN-), U12.2 (GND), U12.4 (IN-), U13.2 (GND), U13.4 (IN-), U14.2 (GND), U14.4 (IN-), U15.2 (GND), U15.4 (IN-), U16.2 (GND), U16.4 (IN-), U17.2 (GND), U17.4 (IN-), U18.2 (GND), U18.4 (IN-), U19.2 (GND), U19.4 (IN-), U20.2 (GND), U20.4 (IN-), U21.2 (GND), U21.4 (IN-), U22.2 (GND), U22.4 (IN-), U23.2 (GND), U23.4 (IN-), U24.2 (GND), U24.4 (IN-), U25.2 (GND), U25.4 (IN-), U26.2 (GND), U26.4 (IN-), U27.2 (GND), U27.4 (IN-), U28.2 (GND), U28.4 (IN-), U29.2 (GND), U29.4 (IN-), U30.2 (GND), U30.4 (IN-), U31.2 (GND), U31.4 (IN-), U32.2 (GND), U32.4 (IN-), U33.2 (GND), U33.4 (IN-), U34.2 (GND), U34.4 (IN-), U35.2 (GND), U35.4 (IN-), U36.2 (GND), U36.4 (IN-), U37.2 (GND), U37.4 (IN-), U38.2 (GND), U38.4 (IN-), U39.2 (GND), Y1.2, Y1.4
unnamed: C2.1, R5.2, Y1.3
unnamed: D_0A1.2 (A), D_1A1.2 (A), D_2A1.2 (A), D_3A1.2 (A), D_4A1.2 (A), D_5A1.2 (A), D_6A1.2 (A), D_7A1.2 (A), D_8A1.2 (A), D_9A1.2 (A), D_AA1.2 (A), D_BA1.2 (A), D_CA1.2 (A), D_DA1.2 (A), D_EA1.2 (A), D_FA1.2 (A), D_GA1.2 (A), D_HA1.2 (A), R19.2
unnamed: D_0B1.2 (A), D_1B1.2 (A), D_2B1.2 (A), D_3B1.2 (A), D_4B1.2 (A), D_5B1.2 (A), D_6B1.2 (A), D_7B1.2 (A), D_8B1.2 (A), D_9B1.2 (A), D_AB1.2 (A), D_BB1.2 (A), D_CB1.2 (A), D_DB1.2 (A), D_EB1.2 (A), D_FB1.2 (A), D_GB1.2 (A), D_HB1.2 (A), R20.2
unnamed: D_0C1.2 (A), D_1C1.2 (A), D_2C1.2 (A), D_3C1.2 (A), D_4C1.2 (A), D_5C1.2 (A), D_6C1.2 (A), D_7C1.2 (A), D_8C1.2 (A), D_9C1.2 (A), D_AC1.2 (A), D_BC1.2 (A), D_CC1.2 (A), D_DC1.2 (A), D_EC1.2 (A), D_FC1.2 (A), D_GC1.2 (A), D_HC1.2 (A), R21.2
unnamed: D_0D1.2 (A), D_1D1.2 (A), D_2D1.2 (A), D_3D1.2 (A), D_4D1.2 (A), D_5D1.2 (A), D_6D1.2 (A), D_7D1.2 (A), D_8D1.2 (A), D_9D1.2 (A), D_AD1.2 (A), D_BD1.2 (A), D_CD1.2 (A), D_DD1.2 (A), D_ED1.2 (A), D_FD1.2 (A), D_GD1.2 (A), D_HD1.2 (A), R22.2
unnamed: D_0E1.2 (A), D_1E1.2 (A), D_2E1.2 (A), D_3E1.2 (A), D_4E1.2 (A), D_5E1.2 (A), D_6E1.2 (A), D_7E1.2 (A), D_8E1.2 (A), D_9E1.2 (A), D_AE1.2 (A), D_BE1.2 (A), D_CE1.2 (A), D_DE1.2 (A), D_EE1.2 (A), D_FE1.2 (A), D_GE1.2 (A), D_HE1.2 (A), R23.2
unnamed: D_0F1.2 (A), D_1F1.2 (A), D_2F1.2 (A), D_3F1.2 (A), D_4F1.2 (A), D_5F1.2 (A), D_6F1.2 (A), D_7F1.2 (A), D_8F1.2 (A), D_9F1.2 (A), D_AF1.2 (A), D_BF1.2 (A), D_CF1.2 (A), D_DF1.2 (A), D_EF1.2 (A), D_FF1.2 (A), D_GF1.2 (A), D_HF1.2 (A), R24.2
unnamed: D_0G1.2 (A), D_1G1.2 (A), D_2G1.2 (A), D_3G1.2 (A), D_4G1.2 (A), D_5G1.2 (A), D_6G1.2 (A), D_7G1.2 (A), D_8G1.2 (A), D_9G1.2 (A), D_AG1.2 (A), D_BG1.2 (A), D_CG1.2 (A), D_DG1.2 (A), D_EG1.2 (A), D_FG1.2 (A), D_GG1.2 (A), D_HG1.2 (A), R25.2
unnamed: D_0H1.2 (A), D_1H1.2 (A), D_2H1.2 (A), D_3H1.2 (A), D_4H1.2 (A), D_5H1.2 (A), D_6H1.2 (A), D_7H1.2 (A), D_8H1.2 (A), D_9H1.2 (A), D_AH1.2 (A), D_BH1.2 (A), D_CH1.2 (A), D_DH1.2 (A), D_EH1.2 (A), D_FH1.2 (A), D_GH1.2 (A), D_HH1.2 (A), R26.2
unnamed: D_1.2 (A), D_2.2 (A), D_3.2 (A), D_4.2 (A), D_5.2 (A), D_6.2 (A), D_7.2 (A), D_8.2 (A), D_9.2 (A), D_10.2 (A), D_A1.2 (A), D_B1.2 (A), D_C1.2 (A), D_D1.2 (A), D_E1.2 (A), D_F1.2 (A), D_G1.2 (A), D_H1.2 (A), R9.2
unnamed: D_11.2 (A), D_12.2 (A), D_13.2 (A), D_14.2 (A), D_15.2 (A), D_16.2 (A), D_17.2 (A), D_18.2 (A), D_19.2 (A), D_20.2 (A), D_A2.2 (A), D_B2.2 (A), D_C2.2 (A), D_D2.2 (A), D_E2.2 (A), D_F2.2 (A), D_G2.2 (A), D_H2.2 (A), R10.2
unnamed: D_21.2 (A), D_22.2 (A), D_23.2 (A), D_24.2 (A), D_25.2 (A), D_26.2 (A), D_27.2 (A), D_28.2 (A), D_29.2 (A), D_30.2 (A), D_A3.2 (A), D_B3.2 (A), D_C3.2 (A), D_D3.2 (A), D_E3.2 (A), D_F3.2 (A), D_G3.2 (A), D_H3.2 (A), R11.2
unnamed: D_31.2 (A), D_32.2 (A), D_33.2 (A), D_34.2 (A), D_35.2 (A), D_36.2 (A), D_37.2 (A), D_38.2 (A), D_39.2 (A), D_40.2 (A), D_A4.2 (A), D_B4.2 (A), D_C4.2 (A), D_D4.2 (A), D_E4.2 (A), D_F4.2 (A), D_G4.2 (A), D_H4.2 (A), R12.2
unnamed: D_41.2 (A), D_42.2 (A), D_43.2 (A), D_44.2 (A), D_45.2 (A), D_46.2 (A), D_47.2 (A), D_48.2 (A), D_49.2 (A), D_50.2 (A), D_A5.2 (A), D_B5.2 (A), D_C5.2 (A), D_D5.2 (A), D_E5.2 (A), D_F5.2 (A), D_G5.2 (A), D_H5.2 (A), R13.2
unnamed: D_51.2 (A), D_52.2 (A), D_53.2 (A), D_54.2 (A), D_55.2 (A), D_56.2 (A), D_57.2 (A), D_58.2 (A), D_59.2 (A), D_60.2 (A), D_A6.2 (A), D_B6.2 (A), D_C6.2 (A), D_D6.2 (A), D_E6.2 (A), D_F6.2 (A), D_G6.2 (A), D_H6.2 (A), R14.2
unnamed: D_61.2 (A), D_62.2 (A), D_63.2 (A), D_64.2 (A), D_65.2 (A), D_66.2 (A), D_67.2 (A), D_68.2 (A), D_69.2 (A), D_70.2 (A), D_A7.2 (A), D_B7.2 (A), D_C7.2 (A), D_D7.2 (A), D_E7.2 (A), D_F7.2 (A), D_G7.2 (A), D_H7.2 (A), R15.2
unnamed: D_71.2 (A), D_72.2 (A), D_73.2 (A), D_74.2 (A), D_75.2 (A), D_76.2 (A), D_77.2 (A), D_78.2 (A), D_79.2 (A), D_80.2 (A), D_A8.2 (A), D_B8.2 (A), D_C8.2 (A), D_D8.2 (A), D_E8.2 (A), D_F8.2 (A), D_G8.2 (A), D_H8.2 (A), R16.2
unnamed: D_81.2 (A), D_82.2 (A), D_83.2 (A), D_84.2 (A), D_85.2 (A), D_86.2 (A), D_87.2 (A), D_88.2 (A), D_89.2 (A), D_90.2 (A), D_A9.2 (A), D_B9.2 (A), D_C9.2 (A), D_D9.2 (A), D_E9.2 (A), D_F9.2 (A), D_G9.2 (A), D_H9.2 (A), R17.2
unnamed: D_91.2 (A), D_92.2 (A), D_93.2 (A), D_94.2 (A), D_95.2 (A), D_96.2 (A), D_97.2 (A), D_98.2 (A), D_99.2 (A), D_100.2 (A), D_A10.2 (A), D_B10.2 (A), D_C10.2 (A), D_D10.2 (A), D_E10.2 (A), D_F10.2 (A), D_G10.2 (A), D_H10.2 (A), R18.2
unnamed: R2.1, SW2.1
unnamed: R8.2, U2.66 (USB_DM)
unnamed: R7.2, U2.67 (USB_DP)
